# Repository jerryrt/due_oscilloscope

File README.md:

# due_oscilloscope

A 12-bit oscilloscope and signal generator built on the Arduino Due
(Atmel SAM3X8E, Cortex-M3), streaming samples over USB to a host for
FFT/DSP and visualisation. **MCK runs at 90 MHz, not the Due's usual
84, which is out of specification** (ADC clock 22.5 MHz against a 20 MHz
limit); every RC in this project divides 45 MHz because of it. The
78 MHz in-spec build is retired.

The board does acquisition and generation only. All signal processing and
rendering happens on the host, where numpy/scipy are available and the
missing FPU on the Cortex-M3 stops mattering.

## Documents

| Document | Contents |
|---|---|
| [docs/scope.md](docs/scope.md) | Goals, phases, targets, non-goals |
| [docs/hardware.md](docs/hardware.md) | SAM3X8E and Due facts, measured USB topology |
| [docs/toolchain.md](docs/toolchain.md) | the compilers, the Arduino core sources, and what a bench still installs |
| [docs/build-container.md](docs/build-container.md) | The pinned build container: how to run it, the checks it carries, what it will not do, and what a bench gives up without it |
| [docs/architecture.md](docs/architecture.md) | DMA datapath, timebase, buffering |
| [docs/protocol.md](docs/protocol.md) | Host streaming frame format |
| [docs/awg.md](docs/awg.md) | Both generators, shapes, resolution, and why a trace shakes |
| [docs/measurement-suite.md](docs/measurement-suite.md) | How a figure earns the word baseline, and what is still missing |
| [docs/debugging.md](docs/debugging.md) | Probeless bring-up strategy |
| [docs/dac-open-ended-montreal5.md](docs/dac-open-ended-montreal5.md) | The DAC and the noise/SINAD loop with a Rigol scope on the pins, and how much of the noise the probes add |
| [docs/rtos.md](docs/rtos.md) | Bare-metal and FreeRTOS integration |
| [docs/usb.md](docs/usb.md) | Measured transport ceilings and host I/O policy |
| [docs/testing.md](docs/testing.md) | On-hardware pytest suite: design, and what it found |
| [docs/control-protocol.md](docs/control-protocol.md) | Control over the native port's second CDC function |
| [docs/shared-source.md](docs/shared-source.md) | What the tracks share, and why the wire contract is one of them |
| [docs/issue5.md](docs/issue5.md) | The wrap displacement: the defect, its cause and the chain of evidence, and what the chase teaches |
| [docs/issue5-impact.md](docs/issue5-impact.md) | What the displacement costs the instrument |
| [docs/issue5-campaign.md](docs/issue5-campaign.md) | The three-bench protocol for measuring the displacement, and how to read it |
| [docs/ets.md](docs/ets.md) | Equivalent-time sampling: the math, and the edge resolution this hardware can give |
| [docs/ets-mode.md](docs/ets-mode.md) | ETS PRBS capture and eye: how to run it, the DAC/ADC RC pairing rule, what has been measured, the tools, the limits and the plan |
| [docs/ets-pam.md](docs/ets-pam.md) | ETS PAM4 to PAM256: the pattern for each level count, the levels, the pass and fail gates fixed in advance, and how the two benches split and check each other |
| [docs/noise.md](docs/noise.md) | How much of the converter this board leaves you |
| [docs/frontend.md](docs/frontend.md) | Front end architecture: daemon, GUI, recording |
| [docs/daemon-api.md](docs/daemon-api.md) | The daemon's socket API |
| [docs/hardware-next.md](docs/hardware-next.md) | Options for a more powerful successor |
| [docs/related-work.md](docs/related-work.md) | Comparable instruments, what to read in each, and the gap to the nearest one |
| [docs/analog-validation-plan.md](docs/analog-validation-plan.md) | Re-evaluating the converters' analog performance at 90 MHz: what the loop can judge, and the phases |
| [docs/afe.md](docs/afe.md) | The analog front end's requirements, in one place: the Due as measured, the real-time and equivalent-time capture modes, scope inputs, differential mode, AWG output, protection, power, construction, the tests that accept them, and the decisions the owner owes |
| [docs/afe-plan.md](docs/afe-plan.md) | Building the AFE: the steps, the simulation gate before any build, the bench tests, and the owner's side of the loop with the contractor |
| [docs/stack-depth.md](docs/stack-depth.md) | Worst-case stack depth: the bounds, and what refuses to be guessed |
| [docs/status.md](docs/status.md) | What works, measured figures, recorded mistakes |
| [docs/windows.md](docs/windows.md) | Windows validation: 0c settled, byte loss is macOS's |
| [docs/linux.md](docs/linux.md) | Native Linux bring-up on `linux-x1`, tier 1 |
| [docs/writing.md](docs/writing.md) | How to write one of these |
| `docs/metric-baseline-*.md` | Generated metric reports, one per host and track. Written by the tool, not by hand |
| [CONTRIBUTING.md](CONTRIBUTING.md) | Commit, branch, version and release conventions |
| [docs/versioning.md](docs/versioning.md) | The one project version and how a release is cut |
| [CLAUDE.md](CLAUDE.md) | Agent working instructions |

**Current state is not in the checkout.** What is current and what to
pick up live on standing GitHub issues, edited in place: **#71** across
all benches, **#31** mac-bench, **#32** linux-x1, **#34** windows-desk.
They go stale by design, which is why they are issues and not files.

## Status

**The complete loop works, solidly**: the host streams a waveform to
the DAC over bulk OUT while simultaneously capturing it back from the
ADC over bulk IN, on Track B's bare-metal UOTGHS stack. Verified: zero
underruns, zero sequence gaps, zero CRC errors, and tone amplitude at
the theoretical maximum (1371 +/- 2 codes) in every 40 ms window of a
run. See [docs/status.md](docs/status.md).

Those figures are macOS's. Read them with objective 0h in mind: the
playback path there loses 0.45-2.25% of what the host writes above
200 ksps, silently and with `under=0` throughout. It does not on
Windows - [docs/windows.md](docs/windows.md).

**And there is a front end on it.** A daemon owns the ports and the
real-time threads and serves clients over a socket
([docs/daemon-api.md](docs/daemon-api.md)); a Qt window draws from it
with min/max decimation and a health panel
([docs/frontend.md](docs/frontend.md)). Both have test suites that need
no board:

```sh
python3 -m daemon --fake                     # from host/
.venv-gui/bin/python -m gui --spawn-fake     # the front end, no hardware
.venv-gui/bin/python -m gui --spawn-file cap.due   # replay a recording
```

| Measurement | Result |
|---|---|
| Matched loop up to 453,488 sps each way | 1371 +/- 2 codes in every window, `under=0`, gapless |
| AWG play-only up to 1.383 Msps (DACC hardware limit) | `under=0` at a 2.81 MB/s DMA-fed stream |
| Full-rate pair: DAC 907 k + capture 907 k aggregate | runs with `under=0`; purity work remains (#71) |
| Capture path (Track B) | sent by endpoint DMA; the processor never reads a sample |
| USB via endpoint DMA (IN / OUT / duplex) | **32.0 / 26.6 / 16.95 MB/s** on macOS; bytes *offered*, see objective 0h |
| The same three on Windows 11 | IN **29 median (26-34 over 9 runs)** / OUT **37.6-37.8** / duplex **47.7-48.5 MB/s**, OUT with 0 B deficit |

**Validated on a second host.** The same firmware on Windows 11 and a
second board conserves every byte at every playback rate from 200,000 to
1,392,857 sps, captures gapless at 453,488 sps, returns the loop tone at
1370.8 codes, and never wedges in `close()`. That settles objective 0c
and points the playback byte loss at macOS's CDC driver rather than at
the device - see [docs/windows.md](docs/windows.md).

Both tracks stream the ADC's full in-spec output continuously over
plain CDC; Track A is the reference oracle, Track B the project. The
transport was never the limit — most of what looked like device faults
were host-side measurement bugs, all recorded in
[docs/status.md](docs/status.md).

## Tests

The suite runs against the real board over both USB ports; there is no
simulator, because the failures it exists to catch have no software
model. It needs pytest, which is not stdlib, so **the Python side runs
from a venv**:

```sh
python3 -m venv .venv
.venv/bin/pip install -r requirements-dev.txt
.venv/bin/python -m pytest --track=b -q      # or --track=a, or both
.venv/bin/python -m pytest -m smoke -q       # the fast subset
```

`host/` runs from the same venv: it takes pyserial, which finds the
board's ports by USB VID/PID on every platform and is the serial backend
on Windows. `host/scope.py` adds pyusb for the bench oscilloscope. All
of it is declared in `requirements-dev.txt`.

See [docs/testing.md](docs/testing.md).

## Design in one paragraph

Timer Counter outputs trigger the ADC and the DAC in hardware, so
capture is deterministic and generation phase-stable (the host-fed
playback path runs the DAC on its own timer channel). The ADC's PDC
channel writes conversions into a ring of SRAM buffers; the playback
ring feeds the DACC the same way in reverse. The CPU never touches
sample data in the design's end state — playback already reaches it
(the ring is filled by UOTGHS endpoint DMA), and converting the capture
side's remaining FIFO copy is the current objective. A jumper from DAC0 to A0
closes the loop so each half validates the other without any front-end
hardware.

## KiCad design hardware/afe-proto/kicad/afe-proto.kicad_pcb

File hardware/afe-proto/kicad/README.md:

# AFE shield version 1, KiCad 10 project

**Fixed version: AFE full range design 01 (FR-01)**, recorded in [DESIGN-01.md](DESIGN-01.md).

This folder holds version 1's design data and its KiCad files. The tools
that build and check them live in [`../pcbtools`](../pcbtools/README.md)
and run in the pinned PCB image (`docker/pcb/run.sh`). The scripts that
used to live here (`build_sch.py`, `build_pcb.py`, `check.py`,
`lr_check.py`, `route.py` and the rest) were replaced by `pcbtools` and
deleted; the frozen copies under `../tests/fixtures/` are the reference
the replacements were proved against.

| file | role |
|---|---|
| `design.py` | parts and connectivity: every part, its value, LCSC code, footprint and the net on each pin. The one source |
| `layout.py` | the placement data: each part's position and rotation, with the reason beside it |
| `layout_view.py` | an SVG of the board or a window of it, for review |
| `afe-proto.kicad_sch`, `.kicad_pro`, `.kicad_pcb`, `lib/`, `*-lib-table` | the KiCad files, generated from the data by `pcbtools` |
| `render/` | renders and the schematic PDF |
| `3d/` | 3D models KiCad's library lacks, with source, hash and licence (`3d/SOURCES.md`) |

Board configuration (rules tables, fences, board setup) is
`../pcbtools/boards/v1.py`. Build, check and route with the commands in
the `pcbtools` README: `pcbtools.schematic` and `pcbtools.build` write
the files, `pcbtools.schematic_check` and `pcbtools.check --config v1`
check them, and routing uses the image's Freerouting flow
(`docker/pcb/freeroute.sh`).

Edit `design.py`, `layout.py` or `boards/v1.py`, never the generated
KiCad files.

Known, listed in the checks with their reasons:
- One ERC exclusion: the LM27762's PGOOD is tied to GND as its datasheet asks when unused.
- The BNC footprint is the KH-BNC50-3511's, drawn from Kinghelm's drawing (`lib/afe.pretty`). It has no 3D model: EasyEDA's is licensed for JLCEDA/EasyEDA only.
- The XIO0 socket footprint swaps odd and even pad numbers. KiCad's socket has pin 2 at -2.54 mm; the Due has it at +2.54. Its silkscreen pin-1 mark lands on pin 2.

Own work, CC BY-SA 4.0.

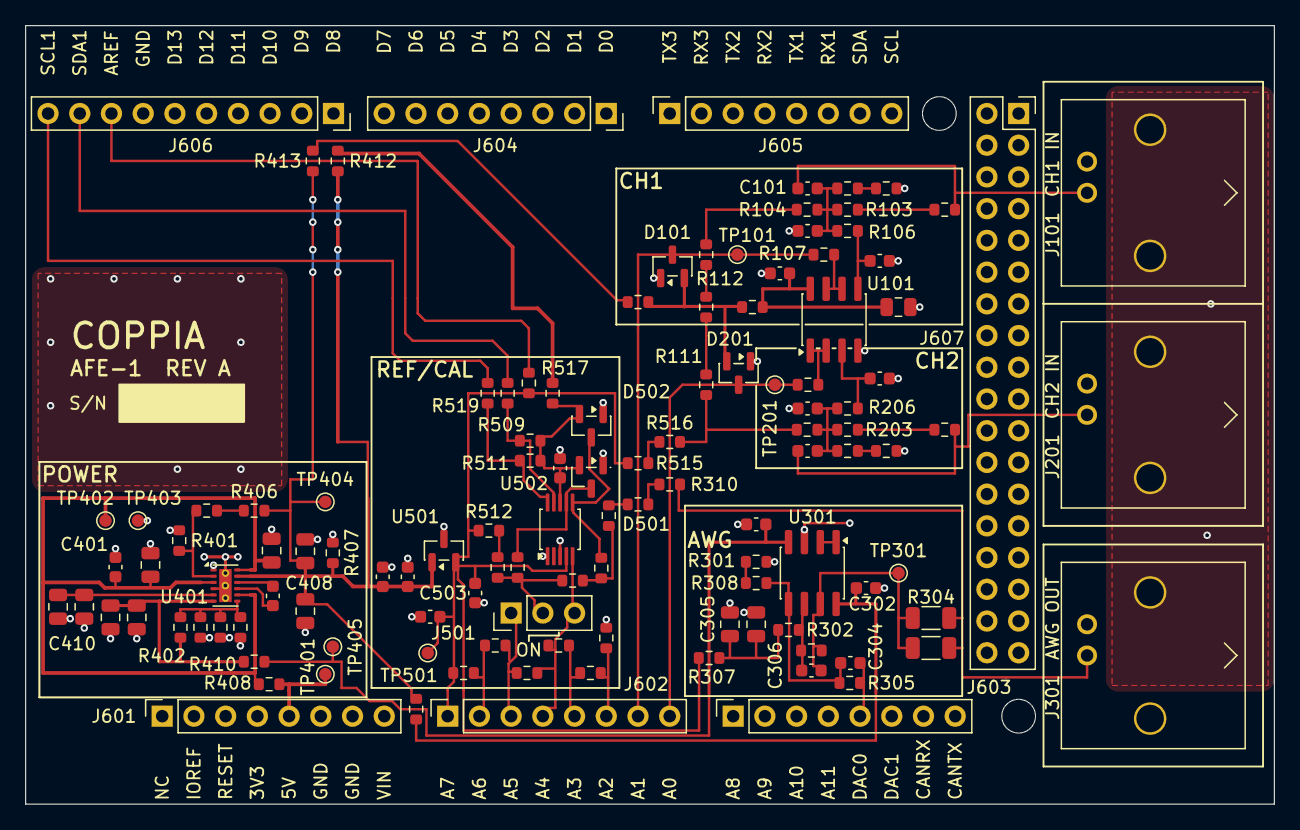
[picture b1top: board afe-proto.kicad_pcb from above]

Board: 2 copper layers, 100.0 x 62.3 mm, 122 parts (0 on the bottom side), 63 nets.

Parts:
C101, C201: 12p C0G; C_0603_1608Metric
C102, C202: 30p C0G; C_0603_1608Metric
C103, C302, C303, C401, C501, C502, C503: 100n X7R; C_0603_1608Metric
C104, C305, C306, C403, C404, C405, C406, C407, C408, C409, C410: 10u X5R 25V; C_0805_2012Metric
C105, C203, C301, C304: 10p C0G; C_0603_1608Metric
C402, C504, C505: 1u X5R; C_0603_1608Metric
D101, D201, D501, D502: BAV99; SOT-23
J101, J201, J301: KH-BNC50-3511; BNC_Kinghelm_KH-BNC50-3511_Horizontal
J501: CAL; PinHeader_1x03_P2.54mm_Vertical
J601: POWER0; PinSocket_1x08_P2.54mm_Vertical
J602: ADCL0; PinSocket_1x08_P2.54mm_Vertical
J603: ADCH0; PinSocket_1x08_P2.54mm_Vertical
J604: PWML0; PinSocket_1x08_P2.54mm_Vertical
J605: COMMUNICATION0; PinSocket_1x08_P2.54mm_Vertical
J606: PWMH0; PinSocket_1x10_P2.54mm_Vertical
J607: XIO0; PinSocket_2x18_P2.54mm_Vertical_DueXIO
MH601, MH602: M2.5 standoff; MountingHole_2.7mm_M2.5
R101, R104, R201, R204, R403, R404, R405: 330k 1%; R_0603_1608Metric
R102, R105, R202, R205: 470k 1%; R_0603_1608Metric
R103, R203: 300k 1%; R_0603_1608Metric
R106, R206: 680 1%; R_0603_1608Metric
R107, R207: 22 1%; R_0603_1608Metric
R108, R408: 1 1%; R_0603_1608Metric
R110, R111, R112, R113, R309, R310, R410, R411, R412, R413, R515, R516, R517, R518, R519, R520: 0R 1%; R_0603_1608Metric
R301, R402, R406: 75k 1%; R_0603_1608Metric
R302: 4.99k 1%; R_0603_1608Metric
R303: 3.3k 1%; R_0603_1608Metric
R304, R306: 100 1% 1206; R_1206_3216Metric
R305, R308: 51k 1%; R_0603_1608Metric
R307, R503: 100 1%; R_0603_1608Metric
R401, R409: 100k 1%; R_0603_1608Metric
R407: 2.2k 1%; R_0603_1608Metric
R501: 22k 1%; R_0603_1608Metric
R502: 15k 1%; R_0603_1608Metric
R504, R505, R506, R507, R508: 270 1%; R_0603_1608Metric
R509, R511: 4.7k 1%; R_0603_1608Metric
R510: 0R; R_0603_1608Metric
R512: 1k 1%; R_0603_1608Metric
R513: 3.9k 1%; R_0603_1608Metric
R514: 13k 1%; R_0603_1608Metric
TP101: A1; TestPoint_Pad_D1.0mm
TP201: A0; TestPoint_Pad_D1.0mm
TP301: AWG_OUT; TestPoint_Pad_D1.0mm
TP401: +5V_DUE; TestPoint_Pad_D1.0mm
TP402: +5V_F; TestPoint_Pad_D1.0mm
TP403: GND; TestPoint_Pad_D1.0mm
TP404: +3V3A; TestPoint_Pad_D1.0mm
TP405: VNEG; TestPoint_Pad_D1.0mm
TP501: VREF; TestPoint_Pad_D1.0mm
U101, U301: TPH2502-SR; SOIC-8_3.9x4.9mm_P1.27mm
U401: LM27762DSSR; WSON-12-1EP_3x2mm_P0.5mm_EP1x2.65_ThermalVias
U501: REF3030EAIDBZR; SOT-23
U502: ADS1115IDGSR; TSSOP-10_3x3mm_P0.5mm

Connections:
/+3V3A: C407.1, C408.1, C501.1, C505.1, R406.1, R407.1, R411.1, R412.1, R413.1, TP404.1, U401.11, U501.1
/+5V_DUE: J601.5, R408.1, TP401.1
/+5V_F: C401.1, C403.1, C404.1, R408.2, TP402.1, U401.3, U401.8, U401.12
/A0: D201.3, J602.8, R207.2, TP201.1
/A1: D101.3, J602.7, R107.2, TP101.1
/AREF: J606.8, R510.2
/AWG_BIN: C304.2, R305.2, R308.1, U301.5
/AWG_BNC: J301.1, R304.2, R306.2, R310.2
/AWG_BPL: R301.1, R308.2
/AWG_I: R309.2, R310.1
/AWG_INV: C301.2, R302.1, R303.2, U301.6
/AWG_OUT: C301.1, R303.1, R304.1, R306.1, TP301.1, U301.7
/AWG_S: R309.1, R501.1
/AWG_SP: U301.1, U301.2
/AWG_X: C305.1, C306.1, R302.2, R307.2
/CH1_IN: C101.1, J101.1, R102.1
/CH1_N: C101.2, C102.1, R103.2, R104.1, R105.1, R106.1
/CH1_NP: C105.1, R106.2, U101.5
/CH1_OUT: R107.1, U101.6, U101.7
/CH1_R1A: R102.2, R103.1
/CH1_R2A: R101.1, R105.2
/CH2_IN: C201.1, J201.1, R202.1
/CH2_N: C201.2, C202.1, R203.2, R204.1, R205.1, R206.1
/CH2_NP: C203.1, R206.2, U101.3
/CH2_OUT: R207.1, U101.1, U101.2
/CH2_R1A: R202.2, R203.1
/CH2_R2A: R201.1, R205.2
/DAC0: C304.1, J603.5, R305.1
/GND: C102.2, C103.2, C104.2, C105.2, C202.2, C203.2, C302.2, C303.2, C305.2, C306.2, C401.2, C403.2, C404.2, C405.2, C406.2, C407.2, C408.2, C409.2, C410.2, C501.2, C502.2, C503.2, C504.2, C505.2, D101.1, D201.1, D501.1, D502.1, J101.2, J201.2, J301.2, J601.6, J601.7, J606.7, J607.35, J607.36, R101.2, R201.2, R301.2, R401.2, R403.2, R404.2, R405.2, R407.2, R503.2, TP403.1, U101.4, U301.3, U401.1, U401.4, U401.13, U501.3, U502.1, U502.3
/LM_C1N: C402.2, U401.9
/LM_C1P: C402.1, U401.10
/LM_CP: C405.1, C406.1, U401.5
/LM_FBN: R402.2, R403.1, R404.1, R405.1, U401.7
/LM_FBP: R401.1, R409.2, U401.2
/LM_FBPX: R406.2, R409.1
/P33_G: C302.1, R411.2, U301.8
/P33_R: C502.1, D501.2, D502.2, R509.2, R511.2, R517.2, U502.8
/P33_RN: R412.2, R517.1
/P33_S: R110.1, R413.2
/P33_U: D101.2, D201.2, R108.1, R110.2
/SCL1: J606.10, R519.1
/SCL1_A: R511.1, R519.2, U502.10
/SC_VCC: C103.1, C104.1, R108.2, U101.8
/SDA1: J606.9, R518.1
/SDA1_A: R509.1, R518.2, U502.9
/SNS_B: J501.2, R502.2, R514.1, R520.1
/SNS_BI: D501.3, R514.2, U502.7
/SNS_B_N: R512.1, R520.2
/SNS_TAP: R501.2, R502.1, R513.1
/SNS_TI: D502.3, R513.2, U502.6
/TAP1: J602.6, R503.1, R504.1
/TAP2: J602.5, R504.2, R505.1
/TAP3: J501.3, J602.4, R505.2, R506.1, U502.5
/TAP4: J501.1, J602.3, R506.2, R507.1
/TAP5: J602.2, R507.2, R508.1
/VNEG: C409.1, C410.1, R402.1, R410.1, U401.6
/VNEG_O: C303.1, R410.2, TP405.1, U301.4
/VREF: C503.1, C504.1, J602.1, R307.1, R508.2, R510.1, R512.2, R515.1, TP501.1, U501.2, U502.4
/VREF_M: R515.2, R516.1
/VREF_P: R111.1, R204.2, R516.2
/VREF_Q: R111.2, R113.1
/VREF_R: R104.2, R112.2
/VREF_S: R112.1, R113.2

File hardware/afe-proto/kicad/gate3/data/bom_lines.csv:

lcsc,class,refs,qty,value,footprint,unit_cny_5,unit_cny_10,unit_cny_20,unit_cny_100,line_usd_20
C118223,Extended,U101 U301,2,TPH2502-SR,Package_SO:SOIC-8_3.9x4.9mm_P1.27mm,2.69,2.69,2.34,1.91,0.6994261119081778
C2837587,Extended,J101 J201 J301,3,KH-BNC50-3511,afe:BNC_Kinghelm_KH-BNC50-3511_Horizontal,4.82,4.82,3.98,3.45,1.7844332855093255
C37593,Extended,U502,1,ADS1115IDGSR,Package_SO:TSSOP-10_3x3mm_P0.5mm,7.83,6.91,6.91,6.04,1.0326996652319465
C473398,Extended,U401,1,LM27762DSSR,Package_SON:WSON-12-1EP_3x2mm_P0.5mm_EP1x2.65_ThermalVias,5.78,4.84,4.84,4.18,0.7233381157340985
C54120492,Extended,U501,1,REF3030EAIDBZR,Package_TO_SOT_SMD:SOT-23,5.58,4.94,4.94,4.33,0.7382831181252989
C14663,Basic,C103 C302 C303 C401 C501 C502 C503,7,100n X7R,Capacitor_SMD:C_0603_1608Metric,0.1,0.1,0.1,0.1,0.10461501673840268
C15849,Basic,C402 C504 C505,3,1u X5R,Capacitor_SMD:C_0603_1608Metric,0.0685,0.0685,0.0685,0.0685,0.030711979913916786
C15850,Basic,C104 C305 C306 C403 C404 C405 C406 C407 C408 C409 C410,11,10u X5R 25V,Capacitor_SMD:C_0805_2012Metric,0.192,0.192,0.144,0.144,0.23672883787661403
C1634,Basic,C105 C203 C301 C304,4,10p C0G,Capacitor_SMD:C_0603_1608Metric,0.06,0.06,0.06,0.06,0.035868005738880916
C1658,Basic,C102 C202,2,30p C0G,Capacitor_SMD:C_0603_1608Metric,0.0306,0.0306,0.0306,0.0306,0.009146341463414634
C17901,Basic,R304 R306,2,100 1% 1206,Resistor_SMD:R_1206_3216Metric,0.0359,0.0359,0.0359,0.0359,0.010730511716881875
C21189,Basic,R110 R111 R112 R113 R309 R310 R410 R411 R412 R413 R515 R516 R517 R518 R519 R520,16,0R 1%,Resistor_SMD:R_0603_1608Metric,0.0128478,0.0128478,0.0128478,0.0128478,0.03072166427546628
C21190,Basic,R512,1,1k 1%,Resistor_SMD:R_0603_1608Metric,0.01,0.01,0.01,0.01,0.0014945002391200382
C22775,Basic,R307 R503,2,100 1%,Resistor_SMD:R_0603_1608Metric,0.0122,0.0122,0.0122,0.0122,0.0036465805834528936
C22797,Basic,R514,1,13k 1%,Resistor_SMD:R_0603_1608Metric,0.0113,0.0113,0.0113,0.0113,0.001688785270205643
C22809,Basic,R502,1,15k 1%,Resistor_SMD:R_0603_1608Metric,0.0174,0.0174,0.0174,0.0174,0.0026004304160688664
C22936,Basic,R108 R408,2,1 1%,Resistor_SMD:R_0603_1608Metric,0.0186,0.0186,0.0186,0.0186,0.005559540889526542
C22966,Basic,R504 R505 R506 R507 R508,5,270 1%,Resistor_SMD:R_0603_1608Metric,0.0102,0.0102,0.0102,0.0102,0.007621951219512195
C22978,Basic,R303,1,3.3k 1%,Resistor_SMD:R_0603_1608Metric,0.013,0.013,0.013,0.013,0.0019428503108560495
C23018,Basic,R513,1,3.9k 1%,Resistor_SMD:R_0603_1608Metric,0.0099,0.0099,0.0099,0.0099,0.001479555236728838
C23024,Basic,R103 R203,2,300k 1%,Resistor_SMD:R_0603_1608Metric,0.0229,0.0229,0.0229,0.0229,0.006844811095169775
C23046,Basic,R302,1,4.99k 1%,Resistor_SMD:R_0603_1608Metric,0.0125,0.0125,0.0125,0.0125,0.001868125298900048
C23137,Basic,R101 R104 R201 R204 R403 R404 R405,7,330k 1%,Resistor_SMD:R_0603_1608Metric,0.0093,0.0093,0.0093,0.0093,0.009729196556671448
C23162,Basic,R509 R511,2,4.7k 1%,Resistor_SMD:R_0603_1608Metric,0.0169,0.0169,0.0169,0.0169,0.005051410808225729
C23178,Basic,R102 R105 R202 R205,4,470k 1%,Resistor_SMD:R_0603_1608Metric,0.0181,0.0181,0.0181,0.0181,0.010820181731229077
C23196,Basic,R305 R308,2,51k 1%,Resistor_SMD:R_0603_1608Metric,0.0101,0.0101,0.0101,0.0101,0.0030188904830224773
C23228,Basic,R106 R206,2,680 1%,Resistor_SMD:R_0603_1608Metric,0.0126,0.0126,0.0126,0.0126,0.0037661406025824963
C23242,Basic,R301 R402 R406,3,75k 1%,Resistor_SMD:R_0603_1608Metric,0.0127,0.0127,0.0127,0.0127,0.005694045911047345
C23345,Basic,R107 R207,2,22 1%,Resistor_SMD:R_0603_1608Metric,0.0101,0.0101,0.0101,0.0101,0.0030188904830224773
C2500,Basic,D101 D201 D501 D502,4,BAV99,Package_TO_SOT_SMD:SOT-23,0.0673,0.0673,0.0673,0.0673,0.04023194643711143
C25803,Basic,R401 R409,2,100k 1%,Resistor_SMD:R_0603_1608Metric,0.0176,0.0176,0.0176,0.0176,0.0052606408417025345
C31850,Basic,R501,1,22k 1%,Resistor_SMD:R_0603_1608Metric,0.0251,0.0251,0.0251,0.0251,0.003751195600191296
C38523,Basic,C101 C201,2,12p C0G,Capacitor_SMD:C_0603_1608Metric,0.0416,0.0416,0.0416,0.0416,0.012434241989478718
C4190,Basic,R407,1,2.2k 1%,Resistor_SMD:R_0603_1608Metric,0.0109,0.0109,0.0109,0.0109,0.0016290052606408416

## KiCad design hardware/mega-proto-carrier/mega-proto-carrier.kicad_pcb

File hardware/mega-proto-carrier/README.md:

# Your Mega PrototypeShield V3 carrier

> **Superseded.** The AFE is now a custom shield PCB ([docs/afe.md](../../docs/afe.md), [hardware/afe-proto](../afe-proto/README.md)). This folder is kept as history and is not used by it.

Open [mega-proto-carrier.kicad_pro](mega-proto-carrier.kicad_pro) in **KiCad 10.x**.
Revision **P3.5** incorporates the seven stripped-board photographs
[IMG_2135](photos/IMG_2135.jpeg) through [IMG_2141](photos/IMG_2141.jpeg).
The PCB records the carrier; the schematic records its contacts and photo-traced nets.
The [P3.1 correction record](routing-corrections.json) links the reviewed R1/R2 and bottom digital-header routes to close-up photo crops.

## Resistor values from the photo

The [IMG_2131 close-up](evidence/resistor-markings-IMG_2131.jpg) clearly shows all three markings, top to bottom:

| Carrier reference | Marking | Nominal value | Traced role |
|---|---|---|---|
| R1 | 103 | 10 kΩ | RESET pull-up |
| R2 | 102 | 1 kΩ | PWR LED series resistor |
| R3 | 102 | 1 kΩ | STAT LED series resistor |

These values are already recorded in the PCB and schematic. They are nominal values decoded from the markings, not resistance measurements. [Structured evidence](resistor-values.json).

## Corrections from the exposed pads

- The parallel main/breakout header rows are approximately **4.064 mm apart**, rather than 2.54 mm. Along each row the pitch remains 2.54 mm. Main header positions, grid registration, switch/LED/resistor placements, SPI transitions and small-hole positions were revised against the newly visible pads.
- J7/J8's first 5 V row remains level with J12. **J3 lies between the D22/D23 and D24/D25 rows.** This corrects P2.1's mistaken assertion that J3 aligned with D22/D23. The bottom 5 V row is near J15; the remaining estimated offset is 0.284 mm.
- SW1's **upper pair is RESET**, joined by front copper. Its **lower pair is GND**, joined by back copper and routed to power-header ground. P2.1's lower-right-pad-to-RESET connection was wrong and has been removed.
- The 103 resistor joins RESET on its right. **IMG_2136 reveals a front diagonal joining R1 left to R2 right / +5 V**, also establishing +5 V at corner pad J9.1.
- The middle 102 resistor's right land reaches **+5 V / J4.3**. Its left land feeds the PWR LED. The two LED left lands share ground through the lower switch pads; LED polarity is still unmeasured.
- The bottom outer digital 5 V pair is **J8.39/J8.40** in this model. Its crossbar is on **B.Cu**, not F.Cu (IMG_2138/2141). The back lower-edge +5 V feed from J13.3 is now included.
- The J13.4 → J7.35 front ground perimeter is moved 1 mm toward the prototyping field, with a vertical departure and chamfer at J13.4. Minimum modeled clearance to other header pad copper is now **1.286 mm**, previously 0.286 mm. See [ground-route-clearance.json](ground-route-clearance.json); these values use provisional CAD pad sizes, not physical measurements.
- J7.31 / D50 now has a horizontal final entry into the pad’s middle-right in the flipped B.Cu view, per your correction. In canonical top view the same segment enters from the left; its D50 net is unchanged.
- IMG_2139 confirms that the D13/STAT back trace departs **inner J1.3**, not outer J10.3. The incorrect back segment between those rows has been removed; their existing front spoke remains. The rest of the D13 dogleg reaches the STAT resistor.
- Former fragments UF-01, UB-02 and UB-03 are now assigned copper. You confirmed UB-01's destination as **J10.2 / GND**. CORNER-HEADER-B now joins J9.5 to J10.2; the final bends under the plastic remain estimated.

The corner pad names below describe **model coordinates in top view**, not a standard ICSP pin-number convention:

| J9 pad | Position | Photo-traced destination |
|---|---|---|
| 1 | upper left | +5 V via R1 left → R2 right copper link |
| 2 | lower left | D50, via lower long front trace / V50 |
| 3 | upper middle | D51, via upper long front trace / V51 |
| 4 | lower middle | D52, via middle long front trace |
| 5 | upper right | GND through corner transition / left-edge back route |
| 6 | lower right | RESET / SW1 upper-left pad |

The default model represents the **normal populated carrier**: SW1, J9 and the main headers are fitted, with SW1/J9's DNP flags cleared. One specimen was stripped solely for backlit routing photography; the other boards retain their switch and header. On that photo specimen, J1-J6's front sockets and SW1/J9 were removed, reverse male pins remain, and J7 is partly stripped. These removals expose the copper; they are not intended assembly omissions. No installed AFE circuit or added hand wiring is visible.

## Review what remains uncertain

Enable **User.5** in **Appearance → Layers**. The **Carrier review questions R2** group contains Q01-Q12, 33 lettered points, enlarged corner/control drawings, and question cards. Entries marked **PHOTO RESOLVED** still await electrical measurements.

[Review picture](preview/review.png) · [Questions](REVIEW-CHECKS.md) · [Measurement sheet](review-checks.csv)

Q02 records your confirmed J9.5 → J10.2 / GND endpoint; Q05 records the photo-resolved R1/R2 supply link. Neither includes a supplied resistance reading. Remaining checks include:

- **Q09:** you confirmed a physical crack near J9 on the photo specimen on 2026-10-30. The other boards have not been assessed for that damage. Circles mark that specimen's nearby SPI/reset routes to check. Copper continuity across the crack remains unmeasured; see [owner-observations.json](owner-observations.json).
- **Q10-Q12:** LED polarity, via features, continuity and mechanical dimensions.

The original P2.1 review and continuity worksheets are archived under `evidence/`; no meter readings have been supplied. Use [continuity.csv](continuity.csv) for the updated route checks with the board removed and unpowered.

## 3D assembly view

Reopen the PCB from disk, then choose **View → 3D Viewer** (**Option+3** on macOS). The normal populated carrier now has **20 component bodies**: six front female sockets, reverse male pin strips (including J7), the corner header, reset switch, two LEDs and three resistors.

[Underside 3D preview](preview/3d-bottom.png). If a viewer filter is active, enable both SMD and through-hole components in the 3D Appearance panel.

The empty grid, empty SMD breakout and outer digital breakout remain bare. Body heights, pin lengths and the generic straight corner header are visual approximations; LED model markings do not establish polarity. Copper, pad locations, net assignments and saved project preferences are unchanged.

Nine unmodified KiCad STEP assets are included under `models/kicad/`, referenced with `${KIPRJMOD}` so another computer does not need these models at an absolute installation path. [Provenance and licensing](models/kicad/README.md) · [Model assignments and verification](models-3d-evidence.json).

`models_3d.py` can restore these per-instance assignments without rebuilding copper. `build_model.py` also applies them during a deliberate baseline rebuild and now preserves an existing `.kicad_pro` file's settings.

## Coordinates and evidence

The owner measured the outline as **103 × 55 mm**. All other dimensions remain photo estimates. Header-row separation is rounded to 4.064 mm; lower main-row y is rounded to 53.5 mm from the overview and control photographs. The fit is not a substitute for a physical measurement.

`PG1.R01C01` is the upper-left prototyping hole, at estimated board-local (3.8, 8.3) mm. Rows increase downward and columns to the right. There are **341 holes** in an irregular 32-column / 15-row pattern at nominal 2.54 mm pitch.

`TP1.T01`–`T14` and `B01`–`B14` identify the empty SMD land rows, left to right. They are coordinate IDs, not an IC pinout. The 28 alternating fanout connections remain modeled; those holes are already connected to SMD lands.

| Lands | Connected grid holes |
|---|---|
| T01, T03, …, T13 | R05C01–R05C07 |
| T02, T04, …, T14 | R04C01–R04C07 |
| B01, B03, …, B13 | R11C01–R11C07 |
| B02, B04, …, B14 | R12C01–R12C07 |

- `F.Cu` / `B.Cu`: interpreted front/back copper, always in top-view coordinates.
- `User.1`: grid IDs; `User.2`: Due names and model labels. These are CAD annotations, not recovered physical silkscreen.
- `User.3` / `User.4`: front/back open-end markers. P3.3 has no remaining open route endpoints or unclassified fragments.
- `User.5`: review overlay; hide it for an ordinary board view.
- [pad-map.csv](pad-map.csv): every pad's board-local coordinates. The native CAD page adds (80, 80) mm.
- [photo-registration.json](photo-registration.json): manually picked image landmarks and projective fits. Close-up grid fit residual describes the picked landmarks only, not absolute mechanical accuracy.
- [model-evidence.json](model-evidence.json): all eleven photo paths/hashes and assembly state.
- [wiring-evidence.json](wiring-evidence.json) / [trace audit](TRACE-AUDIT.md): 28 SMD fanouts, **115 supplemental route sections**, five transition features, approximate bends and provenance.

Physical Mega labels A12-A15 are named DAC0/DAC1/CANRX0/CANTX0 for the Due. Shared Due net names describe the intended interface; a shared name alone does not prove an on-carrier copper connection. No IOREF or additional Due SDA1/SCL1 positions are modeled.

## Keep the carrier separate from the circuit

This project models the board you own. The [AFE prototype project plan](../afe-proto/README.md) uses this corrected carrier as the baseline for a separate working assembly. Complete the AFE simulation before assembling it. Use the [Due V03 PCB](../reference/arduino-due/v03/Arduino-DUE-V03.kicad_pcb) for the owner's Due interface; the [reference index](../reference/arduino-due/README.md) records the power-layout observations and retains V02g separately.

Use the [AFE requirements](../../docs/afe.md) and [plan](../../docs/afe-plan.md) for the circuit. Place planned components by grid addresses, verify existing substrate connections first, and keep planned assembly separate from the photographed carrier. Pad, drill, trace width and via dimensions are provisional; the model is not manufacturing data.

## Files and checks

The project-local `Carrier.pretty/` and `Carrier.kicad_sym` libraries accompany the three native KiCad files. `build_model.py` regenerates the baseline and **overwrites CAD edits**. Once you edit in KiCad, rebuilding must be deliberate. Footprints are locked against accidental movement.

`check_model.py` checks native reload, outline, all pad IDs, SMD fanout endpoints, every recorded route, corrected net assignments, DNP state, header relationships, review circles and schematic/PCB net parity. Its result is [validation.json](validation.json). Native DRC is recorded separately in [drc-review.json](drc-review.json).

KiCad 10.0.6 checks: **244 schematic contacts match the PCB; ERC has zero errors and zero warnings.** All pad centres are inside the outline. The board has **344 track segments and five vias**. DRC has **no shorts, crossing tracks or ordinary clearance violations**. Remaining findings are eleven copper-to-edge clearances. There are no dangling tracks or unrouted connections. Dimensions, hidden copper and physical continuity remain unverified; this is not a clean fabrication DRC.

Run the internal check using KiCad's bundled Python:

```sh
/Applications/KiCad/KiCad.app/Contents/Frameworks/Python.framework/Versions/3.9/bin/python3 hardware/mega-proto-carrier/check_model.py
```

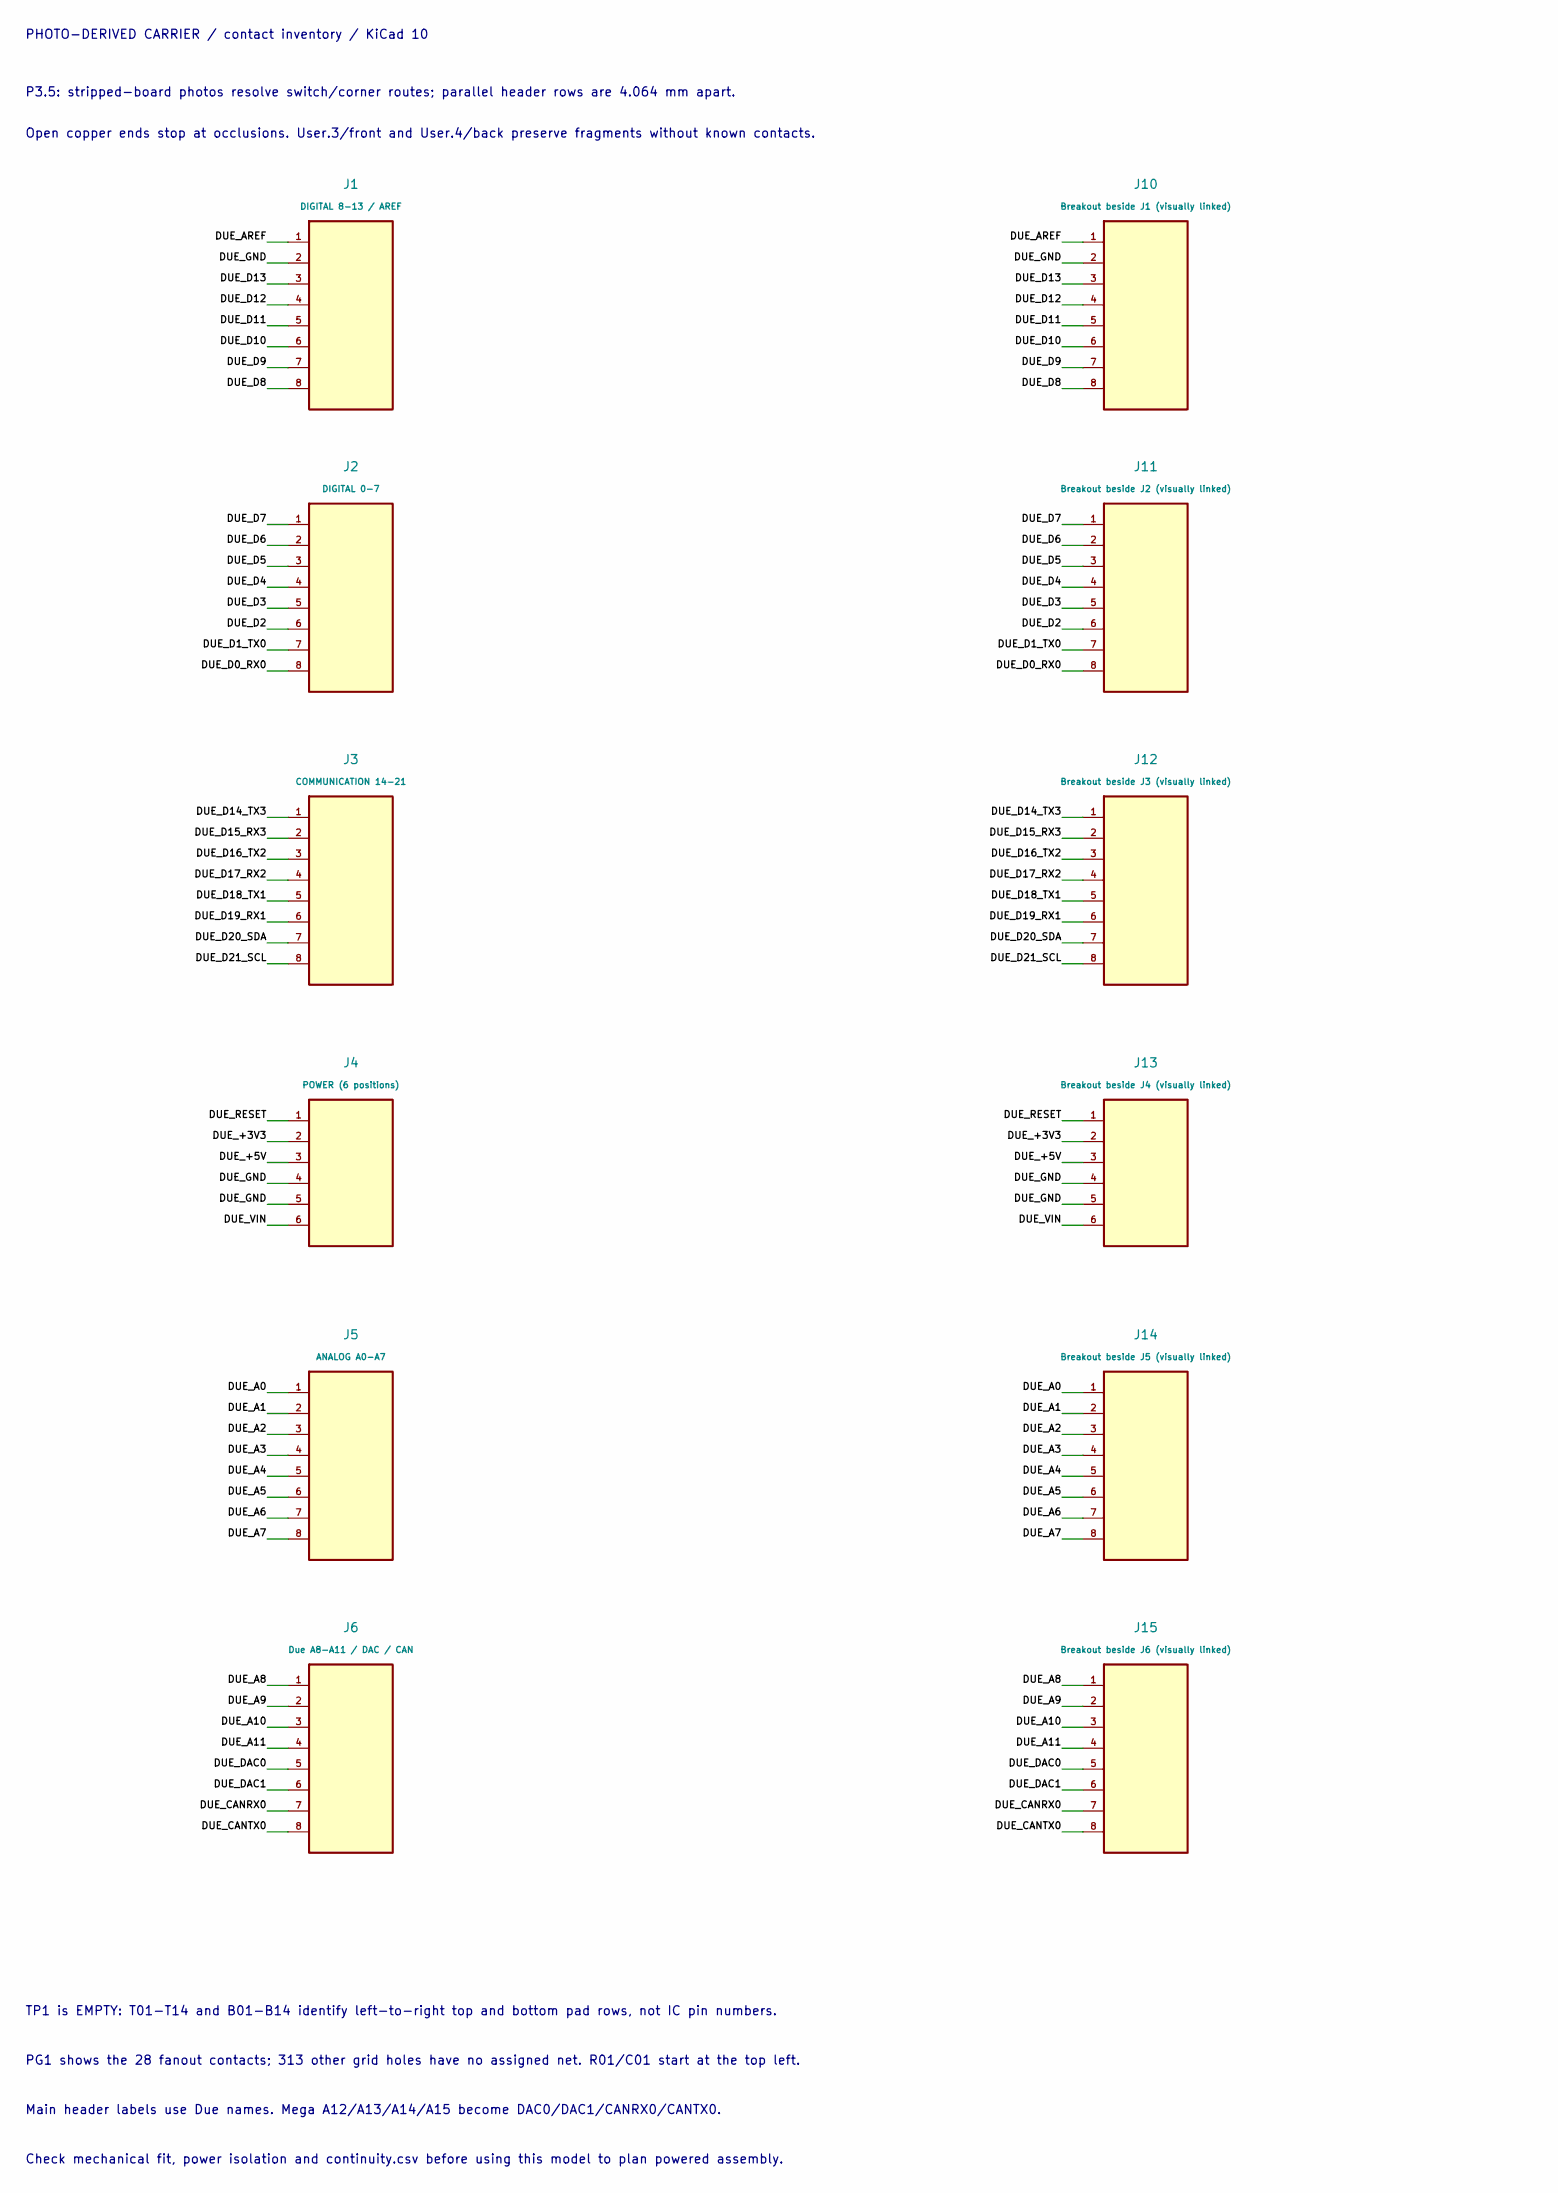
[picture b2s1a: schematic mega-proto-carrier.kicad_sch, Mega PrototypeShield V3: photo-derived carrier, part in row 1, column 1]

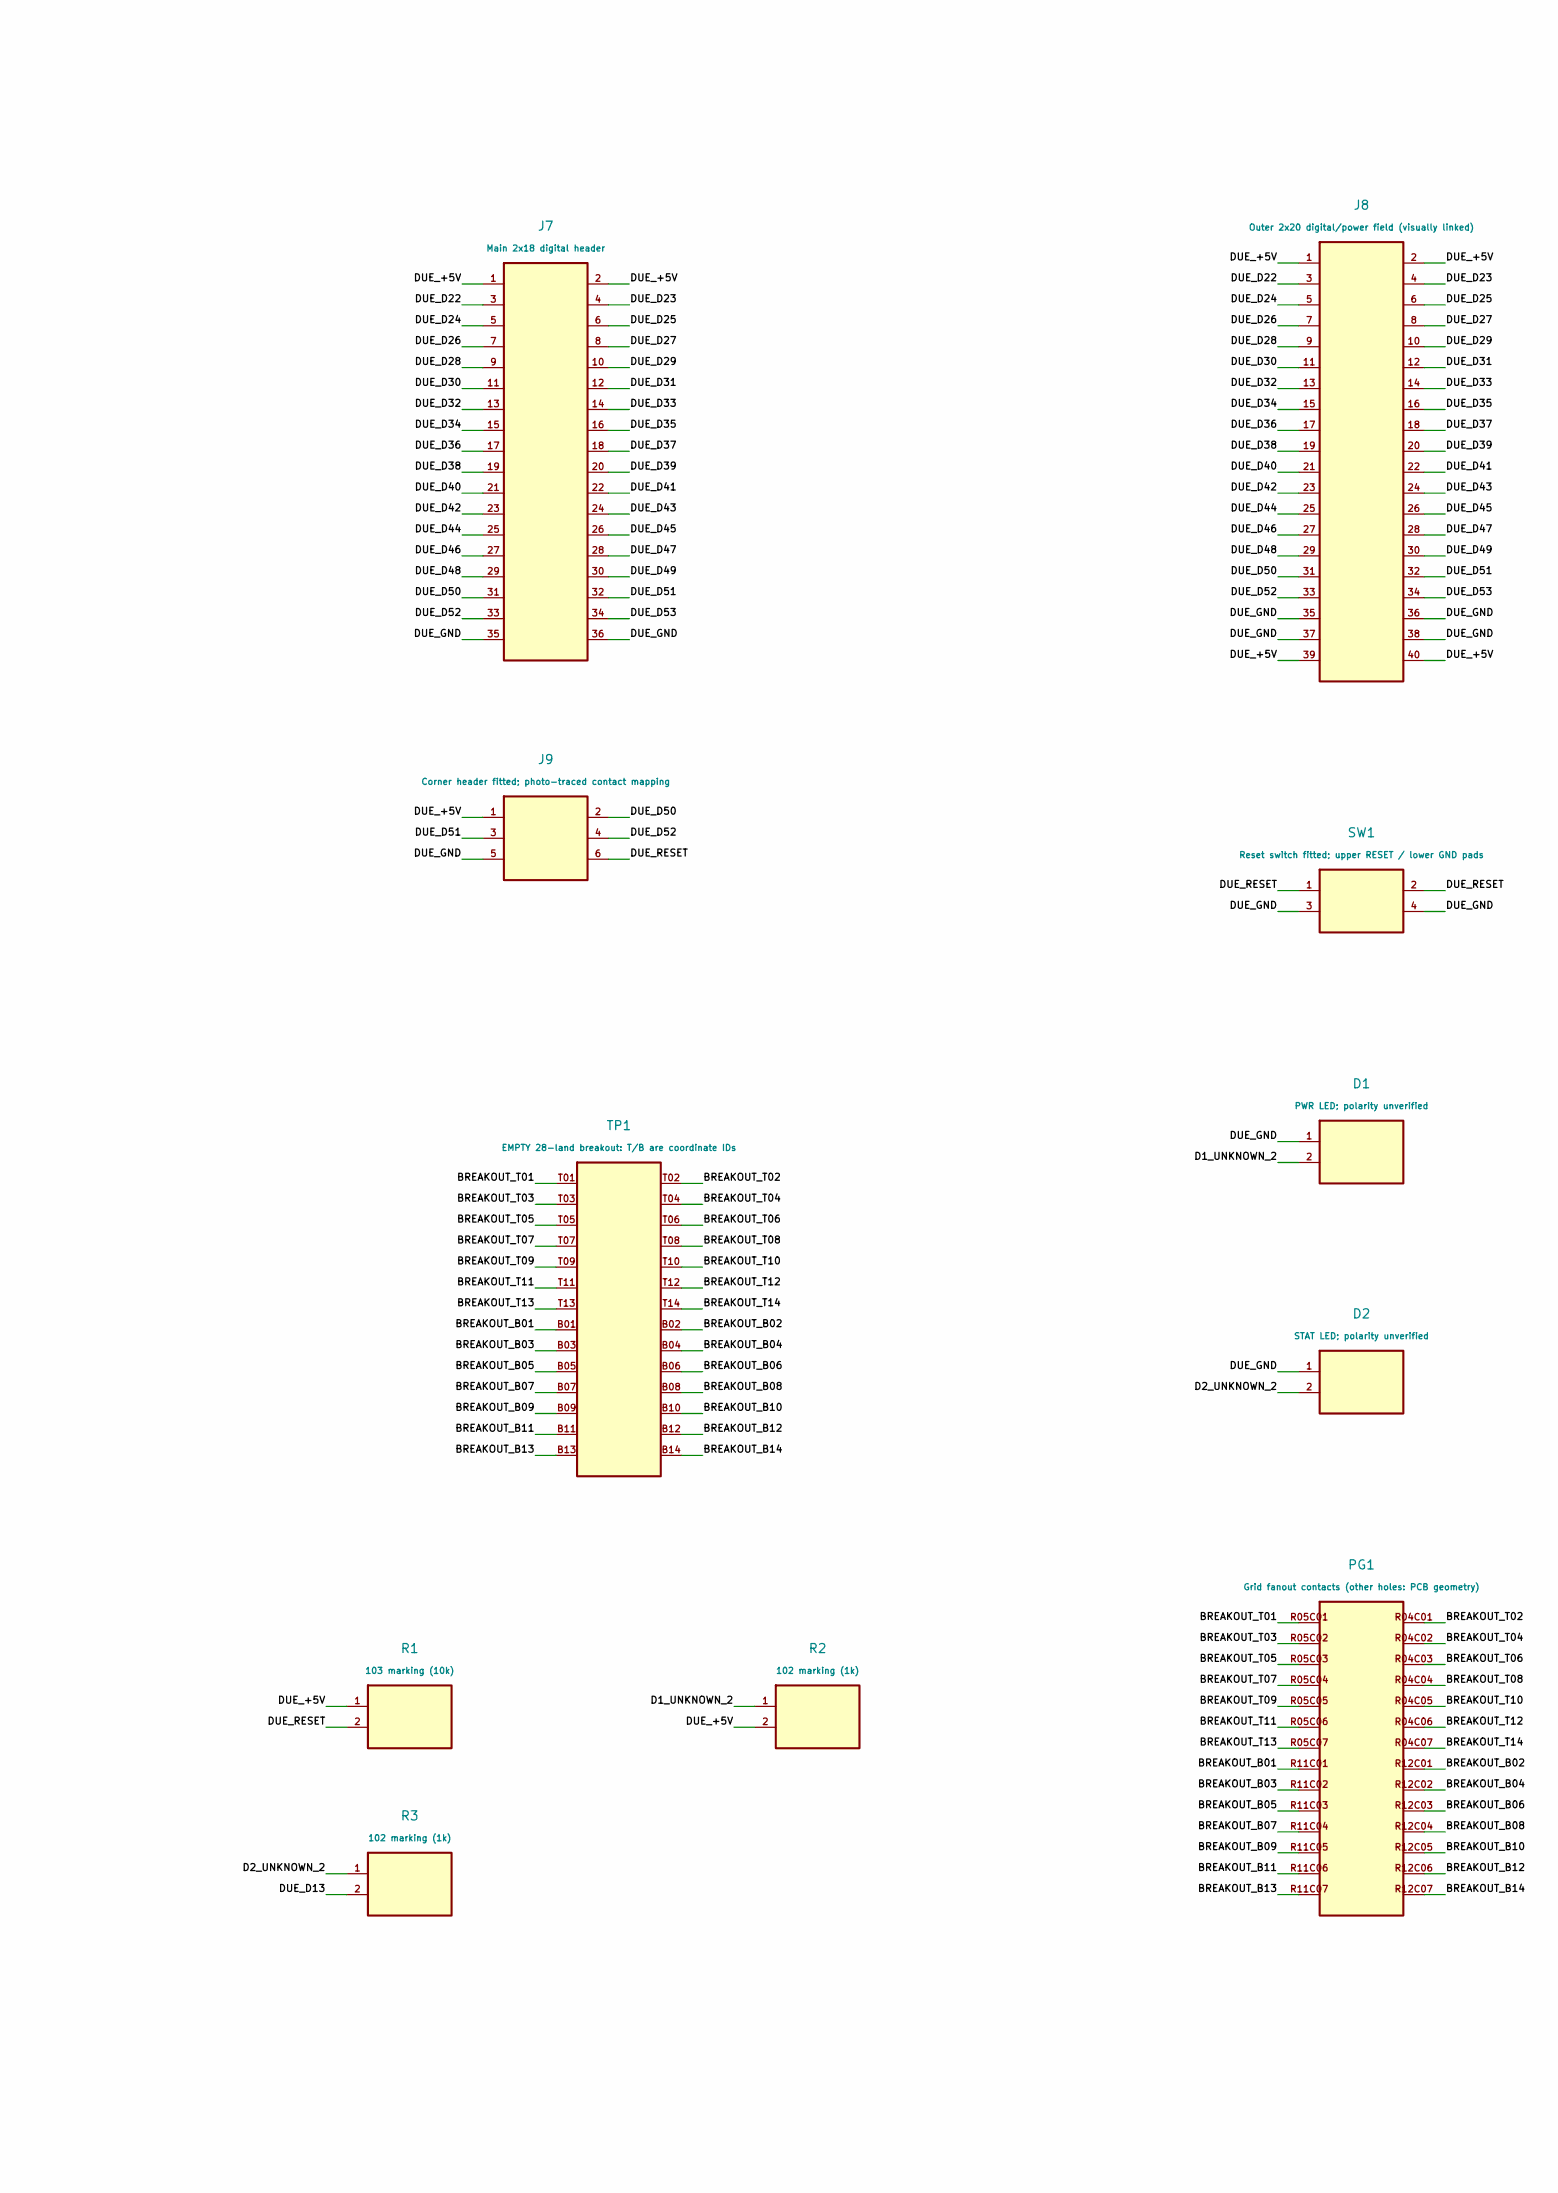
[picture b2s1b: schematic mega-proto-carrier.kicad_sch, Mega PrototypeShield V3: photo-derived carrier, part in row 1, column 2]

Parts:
D1: PWR LED; polarity unverified; LED_estimate
D2: STAT LED; polarity unverified; LED_estimate
J1: DIGITAL 8-13 / AREF; Header_1x08
J2: DIGITAL 0-7; Header_1x08
J3: COMMUNICATION 14-21; Header_1x08
J4: POWER (6 positions); Header_1x06
J5: ANALOG A0-A7; Header_1x08
J6: Due A8-A11 / DAC / CAN; Header_1x08
J7: Main 2x18 digital header; Header_2x18
J8: Outer 2x20 digital/power field (visually linked); Header_2x20
J9: Corner header fitted; photo-traced contact mapping; Corner_3x02
J10: Breakout beside J1 (visually linked); Header_1x08
J11: Breakout beside J2 (visually linked); Header_1x08
J12: Breakout beside J3 (visually linked); Header_1x08
J13: Breakout beside J4 (visually linked); Header_1x06
J14: Breakout beside J5 (visually linked); Header_1x08
J15: Breakout beside J6 (visually linked); Header_1x08
PG1: Grid fanout contacts (other holes: PCB geometry); Grid_32x15_irregular
R1: 103 marking (10k); Passive_estimate
R2, R3: 102 marking (1k); Passive_estimate
SW1: Reset switch fitted; upper RESET / lower GND pads; Switch_6mm_estimate
TP1: EMPTY 28-land breakout: T/B are coordinate IDs; Empty_SMD28

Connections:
/BREAKOUT_B01: PG1.R11C01, TP1.B01
/BREAKOUT_B02: PG1.R12C01, TP1.B02
/BREAKOUT_B03: PG1.R11C02, TP1.B03
/BREAKOUT_B04: PG1.R12C02, TP1.B04
/BREAKOUT_B05: PG1.R11C03, TP1.B05
/BREAKOUT_B06: PG1.R12C03, TP1.B06
/BREAKOUT_B07: PG1.R11C04, TP1.B07
/BREAKOUT_B08: PG1.R12C04, TP1.B08
/BREAKOUT_B09: PG1.R11C05, TP1.B09
/BREAKOUT_B10: PG1.R12C05, TP1.B10
/BREAKOUT_B11: PG1.R11C06, TP1.B11
/BREAKOUT_B12: PG1.R12C06, TP1.B12
/BREAKOUT_B13: PG1.R11C07, TP1.B13
/BREAKOUT_B14: PG1.R12C07, TP1.B14
/BREAKOUT_T01: PG1.R05C01, TP1.T01
/BREAKOUT_T02: PG1.R04C01, TP1.T02
/BREAKOUT_T03: PG1.R05C02, TP1.T03
/BREAKOUT_T04: PG1.R04C02, TP1.T04
/BREAKOUT_T05: PG1.R05C03, TP1.T05
/BREAKOUT_T06: PG1.R04C03, TP1.T06
/BREAKOUT_T07: PG1.R05C04, TP1.T07
/BREAKOUT_T08: PG1.R04C04, TP1.T08
/BREAKOUT_T09: PG1.R05C05, TP1.T09
/BREAKOUT_T10: PG1.R04C05, TP1.T10
/BREAKOUT_T11: PG1.R05C06, TP1.T11
/BREAKOUT_T12: PG1.R04C06, TP1.T12
/BREAKOUT_T13: PG1.R05C07, TP1.T13
/BREAKOUT_T14: PG1.R04C07, TP1.T14
/D1_UNKNOWN_2: D1.2, R2.1
/D2_UNKNOWN_2: D2.2, R3.1
/DUE_+3V3: J4.2, J13.2
/DUE_+5V: J4.3, J7.1, J7.2, J8.1, J8.2, J8.39, J8.40, J9.1, J13.3, R1.1, R2.2
/DUE_A0: J5.1, J14.1
/DUE_A1: J5.2, J14.2
/DUE_A2: J5.3, J14.3
/DUE_A3: J5.4, J14.4
/DUE_A4: J5.5, J14.5
/DUE_A5: J5.6, J14.6
/DUE_A6: J5.7, J14.7
/DUE_A7: J5.8, J14.8
/DUE_A8: J6.1, J15.1
/DUE_A9: J6.2, J15.2
/DUE_A10: J6.3, J15.3
/DUE_A11: J6.4, J15.4
/DUE_AREF: J1.1, J10.1
/DUE_CANRX0: J6.7, J15.7
/DUE_CANTX0: J6.8, J15.8
/DUE_D0_RX0: J2.8, J11.8
/DUE_D1_TX0: J2.7, J11.7
/DUE_D2: J2.6, J11.6
/DUE_D3: J2.5, J11.5
/DUE_D4: J2.4, J11.4
/DUE_D5: J2.3, J11.3
/DUE_D6: J2.2, J11.2
/DUE_D7: J2.1, J11.1
/DUE_D8: J1.8, J10.8
/DUE_D9: J1.7, J10.7
/DUE_D10: J1.6, J10.6
/DUE_D11: J1.5, J10.5
/DUE_D12: J1.4, J10.4
/DUE_D13: J1.3, J10.3, R3.2
/DUE_D14_TX3: J3.1, J12.1
/DUE_D15_RX3: J3.2, J12.2
/DUE_D16_TX2: J3.3, J12.3
/DUE_D17_RX2: J3.4, J12.4
/DUE_D18_TX1: J3.5, J12.5
/DUE_D19_RX1: J3.6, J12.6
/DUE_D20_SDA: J3.7, J12.7
/DUE_D21_SCL: J3.8, J12.8
/DUE_D22: J7.3, J8.3
/DUE_D23: J7.4, J8.4
/DUE_D24: J7.5, J8.5
/DUE_D25: J7.6, J8.6
/DUE_D26: J7.7, J8.7
/DUE_D27: J7.8, J8.8
/DUE_D28: J7.9, J8.9
/DUE_D29: J7.10, J8.10
/DUE_D30: J7.11, J8.11
/DUE_D31: J7.12, J8.12
/DUE_D32: J7.13, J8.13
/DUE_D33: J7.14, J8.14
/DUE_D34: J7.15, J8.15
/DUE_D35: J7.16, J8.16
/DUE_D36: J7.17, J8.17
/DUE_D37: J7.18, J8.18
/DUE_D38: J7.19, J8.19
/DUE_D39: J7.20, J8.20
/DUE_D40: J7.21, J8.21
/DUE_D41: J7.22, J8.22
/DUE_D42: J7.23, J8.23
/DUE_D43: J7.24, J8.24
/DUE_D44: J7.25, J8.25
/DUE_D45: J7.26, J8.26
/DUE_D46: J7.27, J8.27
/DUE_D47: J7.28, J8.28
/DUE_D48: J7.29, J8.29
/DUE_D49: J7.30, J8.30
/DUE_D50: J7.31, J8.31, J9.2
/DUE_D51: J7.32, J8.32, J9.3
/DUE_D52: J7.33, J8.33, J9.4
/DUE_D53: J7.34, J8.34
/DUE_DAC0: J6.5, J15.5
/DUE_DAC1: J6.6, J15.6
/DUE_GND: D1.1, D2.1, J1.2, J4.4, J4.5, J7.35, J7.36, J8.35, J8.36, J8.37, J8.38, J9.5, J10.2, J13.4, J13.5, SW1.3, SW1.4
/DUE_RESET: J4.1, J9.6, J13.1, R1.2, SW1.1, SW1.2
/DUE_VIN: J4.6, J13.6

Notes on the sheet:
PHOTO-DERIVED CARRIER / contact inventory / KiCad 10
P3.5: stripped-board photos resolve switch/corner routes; parallel header rows are 4.064 mm apart.
Open copper ends stop at occlusions. User.3/front and User.4/back preserve fragments without known contacts.
TP1 is EMPTY: T01-T14 and B01-B14 identify left-to-right top and bottom pad rows, not IC pin numbers.
PG1 shows the 28 fanout contacts; 313 other grid holes have no assigned net. R01/C01 start at the top left.
Main header labels use Due names. Mega A12/A13/A14/A15 become DAC0/DAC1/CANRX0/CANTX0.
Check mechanical fit, power isolation and continuity.csv before using this model to plan powered assembly.
